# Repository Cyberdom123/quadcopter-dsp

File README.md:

# Quadcopter design made from scratch

The goal of the project is to create a working model of a quadcopter UAV, which can be
controlled with a Xbox controller. The project utilises the MPU6050 inertial measurement
unit, which combines MEMS accelerometer and gyroscope into a single IC. The combination of
sensor readings from the IMU combined with an adequate mathematical model and a regulating
system allows to make a quadcopter with a stable control system.

# Quadcopter project implementation

The MCU used in the project implementation is STM32F103C6T6, an ARM Cortex-M3 mi-
crocontroller, containing 32Kbytes of ROM. F1303 has built-in hardware support for I2C and
SPI busses used for data transmission between on-board peripherals.
The MPU6050 has been used as a sensor. It is an inertial measurement unit (IMU), a
MEMS integrated circuit combining in itself an accelerometer and a gyroscope. For easy and
intuitive reading of the sensor data at the code level, a library for initialising and handling the
MPU has been written. It uses the built-in I2C bus which is used to exchange data between the
IMU and MCU. The transmission is made in 400kHz mode. In order to save MCU execution
time, a DMA controller has been used, allowing for sending data from RAM to the peripheral.
Similarly, a library for nRF24L01 radio module has been written. nRF is being used for
digital radio transmission between the UAV and a PC. It is connected to the MCU by the
SPI bus and also uses the DMA mechanism. Another nRF connected to the PC is used to
communicate with the quadcopter. The transceivers are used in order to read telemetry data
and for piloting the UAV using an Xbox controller connected to the PC.

To keep the UAV stable it is essential to keep it at a set (stable) angle during movement.
For instance, when we want the drone to fly up vertically, the roll and pitch angle have to be
set to 0 degrees. The IMU supplies the data about displacement and angular velocity and a
suitable mathematical model processes the data in order to estimate the angles.
Finally the integration of data from both sensors with the help of filtration algorithms,
such as complementary filter or Kalman filter allows us to gain precise information about
the angles and for effective stabilisation of the quadcopter during flight. In our project we
used the Kalman filter. It is an aimed at estimating the actual state of the system based
on the observer measurements with Gaussian noise. The algorithm works in two main steps:
estimation of the state of the system based on previous state and correcting it during the next
measurement. Kalman filter uses the mathematical model and data about Gaussian noise in
order to minimalise the estimates and measurement unceirtanties.
The angle estimates and yaw angular velocity is fed into the regulation system consisitng
of three PID regulators for every quantity. The PID regulator works by minimising the difference
between the actual state of the system and a desirable reference state. It contains three
components: proportional (P), which reacts proportionally to current deviateion, integral (I),
which accumulates the deviation as time passes and differential (D), which takes into account
the rate of change of the difference. The output of the PIDs is a duty cycle fed into a signal
mixer, which sets the duty cycle for each of the motors.

More detailed documentation has been placed in the project repository.

## Part list

- Frame: https://www.thingiverse.com/thing:1604440
- 7mm Motor Holder: https://www.thingiverse.com/thing:1675767
- 7x20mm 3.7V DC 46500RPM Motors CCW
- 7x20mm 3.7V DC 46500RPM Motors CW
- Propellers: 55mm
- Transceiver: 2.4GHz NRF24L01
- LiPo Battery: 520mAh 25C 12g Dualsky
- Gyroscope/Accelerometer: MPU6050
- Pressure Sensor: BMP280
- STM32-FC Board (located in the hardware folder)

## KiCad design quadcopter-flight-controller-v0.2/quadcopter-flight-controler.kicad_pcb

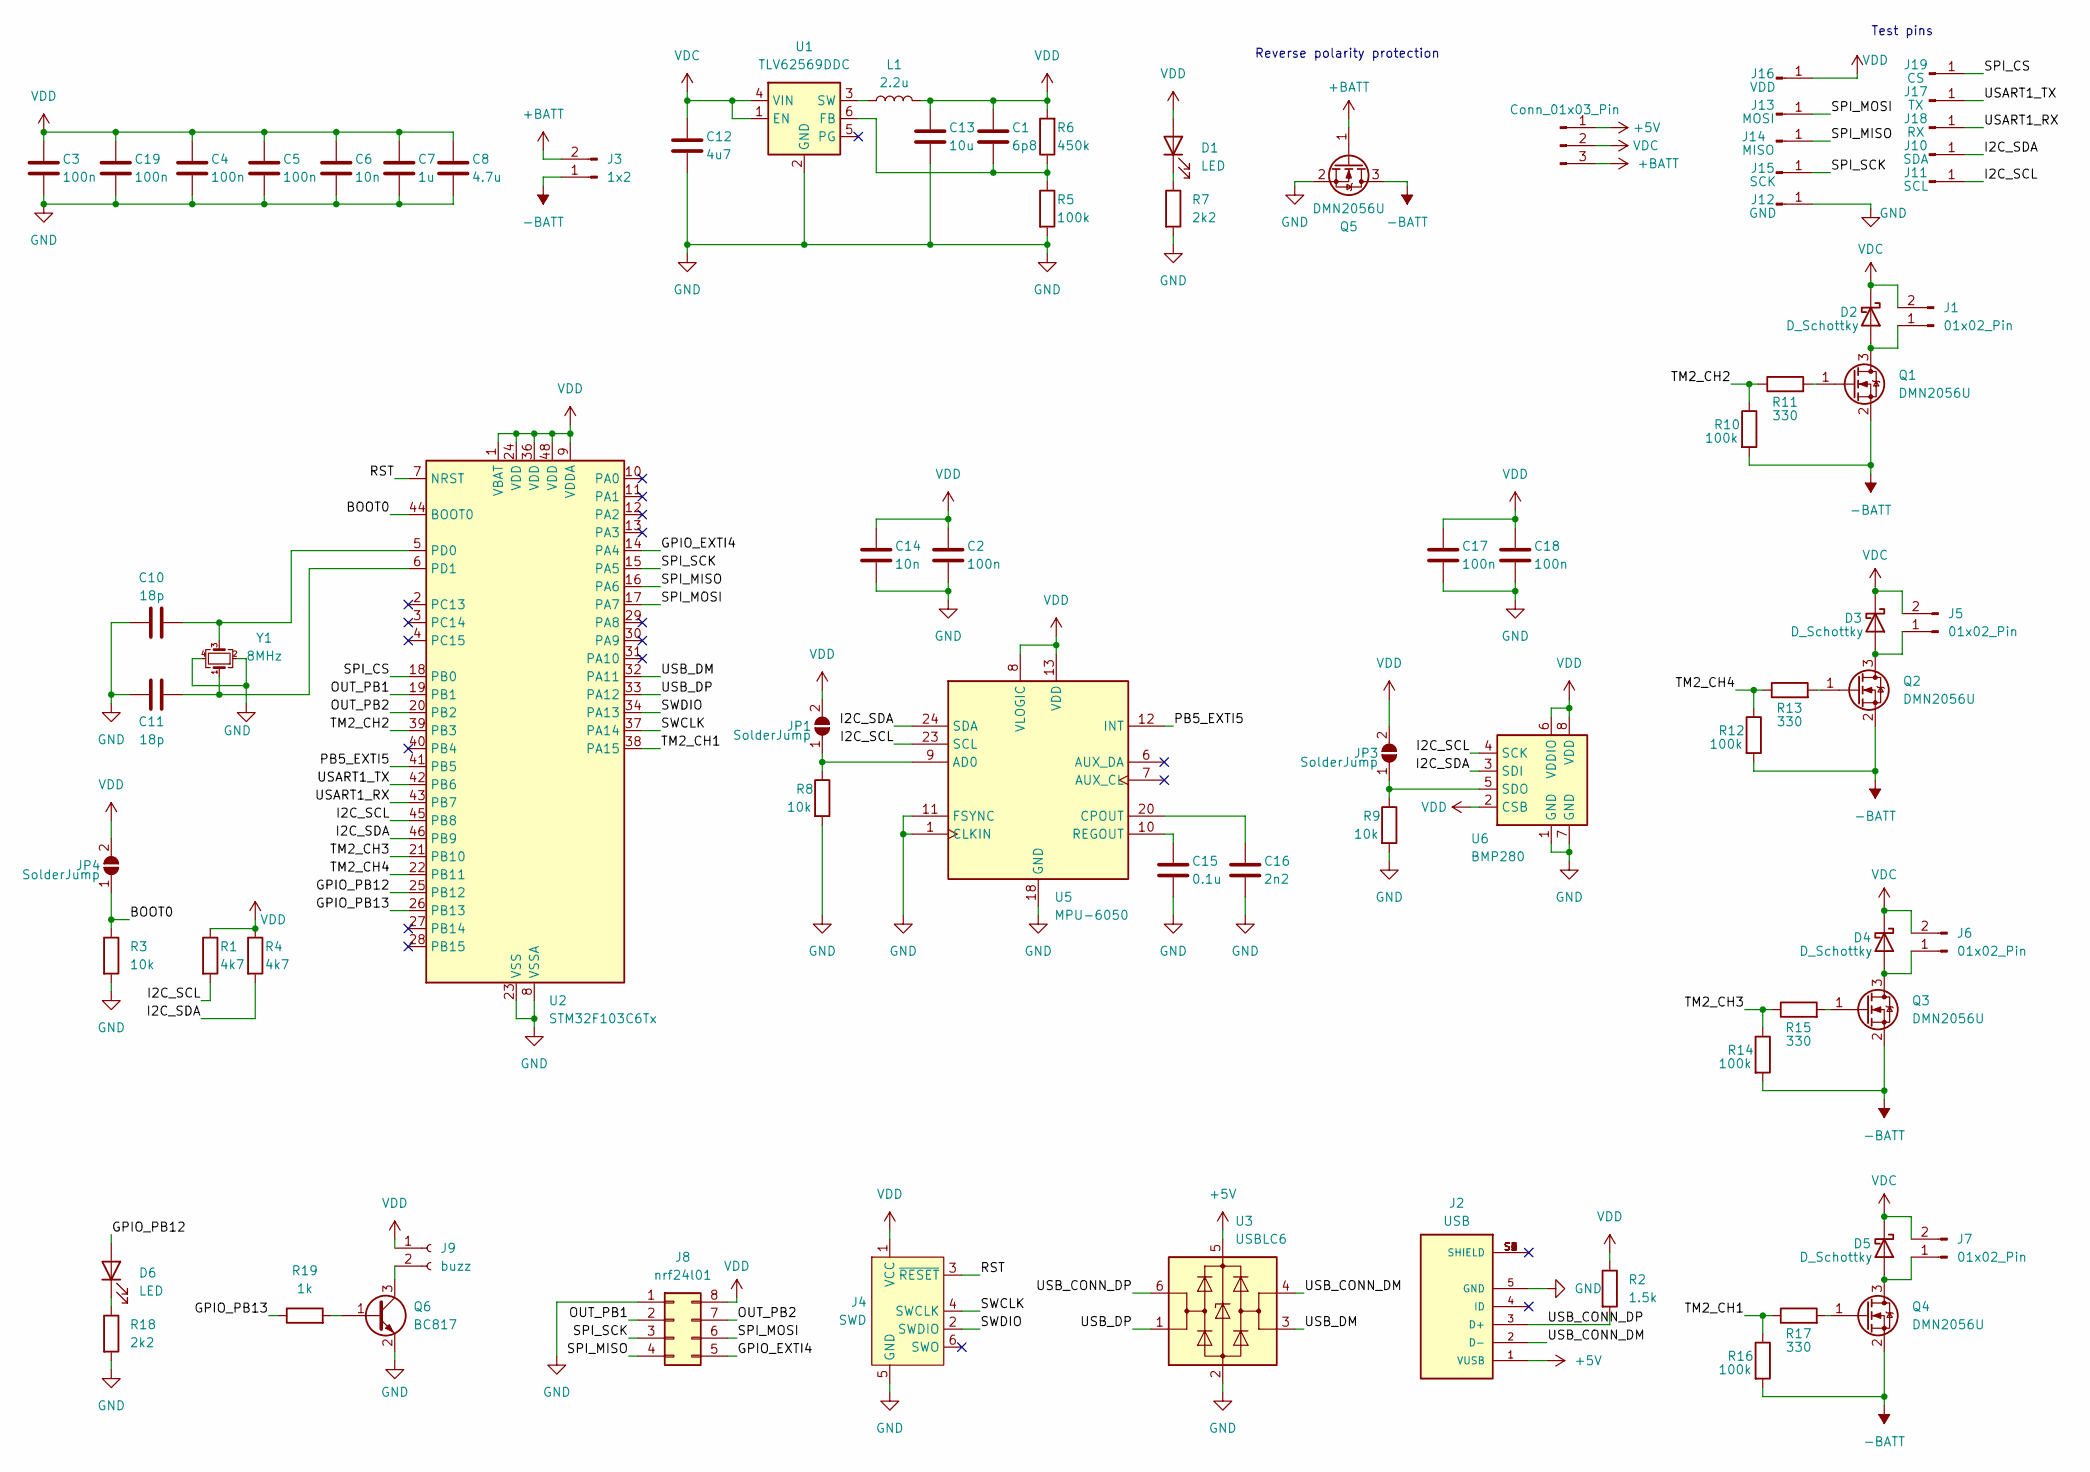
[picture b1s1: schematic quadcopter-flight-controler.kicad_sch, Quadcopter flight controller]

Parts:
C1: 6p8; C_0805_2012Metric
C2, C3, C4, C5, C17, C18, C19: 100n; C_0805_2012Metric
C6, C14: 10n; C_0805_2012Metric
C7: 1u; C_0805_2012Metric
C8: 4.7u; C_1206_3216Metric
C10, C11: 18p; C_0201_0603Metric
C12: 4u7; C_0805_2012Metric
C13: 10u; C_0805_2012Metric
C15: 0.1u; C_0805_2012Metric
C16: 2n2; C_0201_0603Metric
D1, D6: LED; LED_0805_2012Metric
D2, D3, D4, D5: D_Schottky; D_SOD-123F
J1, J5, J6, J7: 01x02_Pin; PinSocket_1x02_P1.27mm_Vertical
J2: USB; AMPHENOL_10118193-0001LF; PARTREV E
J3: 1x2; PinSocket_1x02_P2.54mm_Vertical
J4: SWD; Pin_2x03_P2.54mm
J8: nrf24l01; PinHeader_2x04_P2.54mm_Vertical
J9: buzz; PinSocket_1x02_P1.27mm_Vertical
J10: SDA; TestPoint_Pad_D1.0mm
J11: SCL; TestPoint_Pad_D1.0mm
J12: GND; TestPoint_Pad_D1.0mm
J13: MOSI; TestPoint_Pad_D1.0mm
J14: MISO; TestPoint_Pad_D1.0mm
J15: SCK; TestPoint_Pad_D1.0mm
J16: VDD; TestPoint_Pad_D1.0mm
J17: TX; TestPoint_Pad_D1.0mm
J18: RX; TestPoint_Pad_D1.0mm
J19: CS; TestPoint_Pad_D1.0mm
J20: Conn_01x03_Pin; PinSocket_1x03_P2.54mm_Vertical
JP1, JP3, JP4: SolderJump; SolderJumper-2_P1.3mm_Open_Pad1.0x1.5mm
L1: 2.2u; L_Coilcraft_XxL4040
Q1, Q2, Q3, Q4, Q5: DMN2056U; SOT-23
Q6: BC817; SOT-23
R1, R4: 4k7; R_0805_2012Metric
R2: 1.5k; R_0805_2012Metric
R3, R8, R9: 10k; R_0805_2012Metric
R5, R10, R12, R14, R16: 100k; R_0805_2012Metric
R6: 450k; R_0805_2012Metric
R7, R18: 2k2; R_0805_2012Metric
R11, R13, R15, R17: 330; R_0805_2012Metric
R19: 1k; R_0805_2012Metric
U1: TLV62569DDC; SOT-23-6
U2: STM32F103C6Tx; LQFP-48_7x7mm_P0.5mm
U3: USBLC6; SOT-23-6
U5: MPU-6050; InvenSense_QFN-24_4x4mm_P0.5mm
U6: BMP280; Bosch_LGA-8_2x2.5mm_P0.65mm_ClockwisePinNumbering
Y1: 8MHz; XTAL_QT532S-8.000MAAJ-T

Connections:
+5V: J2.1 (VUSB), J20.1, U3.5 (VBUS)
+BATT: J3.2, J20.3, Q5.1 (G)
-BATT: J3.1, Q1.2 (S), Q2.2 (S), Q3.2 (S), Q4.2 (S), Q5.3 (D), R10.2, R12.2, R14.2, R16.2
/BOOT0: JP4.1 (A), R3.1, U2.44 (BOOT0)
/GPIO_EXTI4: J8.5, U2.14 (PA4)
/GPIO_PB12: D6.2 (A), U2.25 (PB12)
/GPIO_PB13: R19.1, U2.26 (PB13)
/I2C_SCL: J11.1, R1.2, U2.45 (PB8), U5.23 (SCL), U6.4 (SCK)
/I2C_SDA: J10.1, R4.2, U2.46 (PB9), U5.24 (SDA), U6.3 (SDI)
/OUT_PB1: J8.2, U2.19 (PB1)
/OUT_PB2: J8.7, U2.20 (PB2)
/PB5_EXTI5: U2.41 (PB5), U5.12 (INT)
/RST: J4.3 (~RESET), U2.7 (NRST)
/SPI_CS: J19.1, U2.18 (PB0)
/SPI_MISO: J8.4, J14.1, U2.16 (PA6)
/SPI_MOSI: J8.6, J13.1, U2.17 (PA7)
/SPI_SCK: J8.3, J15.1, U2.15 (PA5)
/SWCLK: J4.4 (SWCLK), U2.37 (PA14)
/SWDIO: J4.2 (SWDIO), U2.34 (PA13)
/TM2_CH1: R16.1, R17.1, U2.38 (PA15)
/TM2_CH2: R10.1, R11.1, U2.39 (PB3)
/TM2_CH3: R14.1, R15.1, U2.21 (PB10)
/TM2_CH4: R12.1, R13.1, U2.22 (PB11)
/USART1_RX: J18.1, U2.43 (PB7)
/USART1_TX: J17.1, U2.42 (PB6)
/USB_CONN_DM: J2.2 (D-), U3.4 (I/O2)
/USB_CONN_DP: J2.3 (D+), R2.2, U3.6 (I/O1)
/USB_DM: U2.32 (PA11), U3.3 (I/O2)
/USB_DP: U2.33 (PA12), U3.1 (I/O1)
GND: C2.2, C3.2, C4.2, C5.2, C6.2, C7.2, C8.2, C10.1, C11.1, C12.2, C13.2, C14.2, C15.2, C16.2, C17.2, C18.2, C19.2, J2.5 (GND), J4.5 (GND), J8.1, J12.1, Q5.2 (S), Q6.2 (E), R3.2, R5.2, R7.2, R8.2, R9.2, R18.2, U1.2 (GND), U2.8 (VSSA), U2.23 (VSS), U2.35 (VSS), U2.47 (VSS), U3.2 (GND), U5.1 (CLKIN), U5.11 (FSYNC), U5.18 (GND), U6.1 (GND), U6.7 (GND), Y1.2, Y1.4
unnamed: D1.1 (K), R7.1
unnamed: D2.2 (A), J1.1, Q1.3 (D)
unnamed: D3.2 (A), J5.1, Q2.3 (D)
unnamed: D4.2 (A), J6.1, Q3.3 (D)
unnamed: D5.2 (A), J7.1, Q4.3 (D)
unnamed: D6.1 (K), R18.1
unnamed: J9.2, Q6.3 (C)
unnamed: JP1.1 (A), R8.1, U5.9 (AD0)
unnamed: JP3.1 (A), R9.1, U6.5 (SDO)
unnamed: Q1.1 (G), R11.2
unnamed: Q2.1 (G), R13.2
unnamed: Q3.1 (G), R15.2
unnamed: Q4.1 (G), R17.2
unnamed: Q6.1 (B), R19.2
unnamed: C1.2, R5.1, R6.1, U1.6 (FB)
unnamed: L1.1, U1.3 (SW)
unnamed: C10.2, U2.5 (PD0), Y1.3
unnamed: C11.2, U2.6 (PD1), Y1.1
unnamed: C16.1, U5.20 (CPOUT)
unnamed: C15.1, U5.10 (REGOUT)
VDC: C12.1, D2.1 (K), D3.1 (K), D4.1 (K), D5.1 (K), J1.2, J5.2, J6.2, J7.2, J20.2, U1.1 (EN), U1.4 (VIN)
VDD: C1.1, C2.1, C3.1, C4.1, C5.1, C6.1, C7.1, C8.1, C13.1, C14.1, C17.1, C18.1, C19.1, D1.2 (A), J4.1 (VCC), J8.8, J9.1, J16.1, JP1.2 (B), JP3.2 (B), JP4.2 (B), L1.2, R1.1, R2.1, R4.1, R6.2, U2.1 (VBAT), U2.9 (VDDA), U2.24 (VDD), U2.36 (VDD), U2.48 (VDD), U5.8 (VLOGIC), U5.13 (VDD), U6.2 (CSB), U6.6 (VDDIO), U6.8 (VDD)

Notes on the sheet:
Test pins
Reverse polarity protection

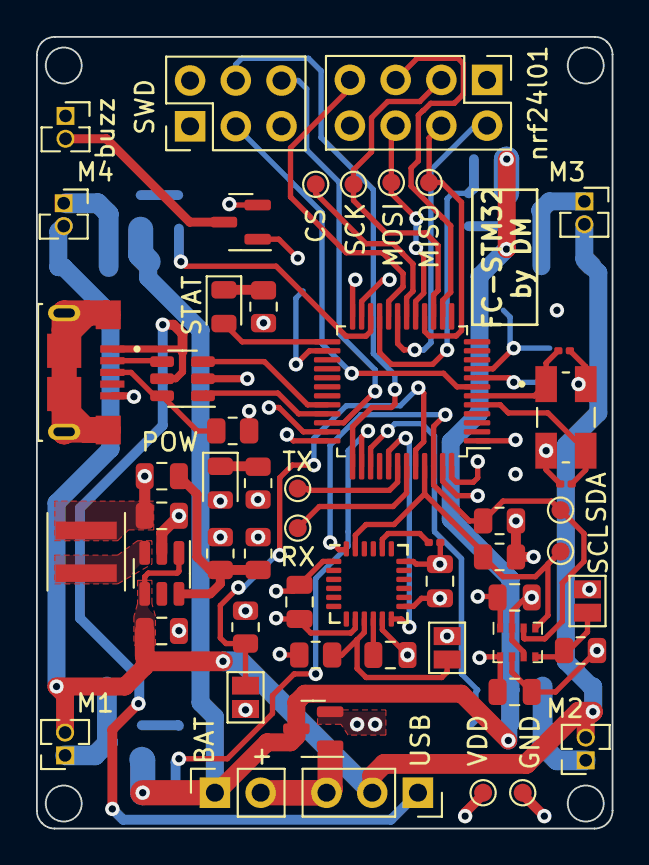
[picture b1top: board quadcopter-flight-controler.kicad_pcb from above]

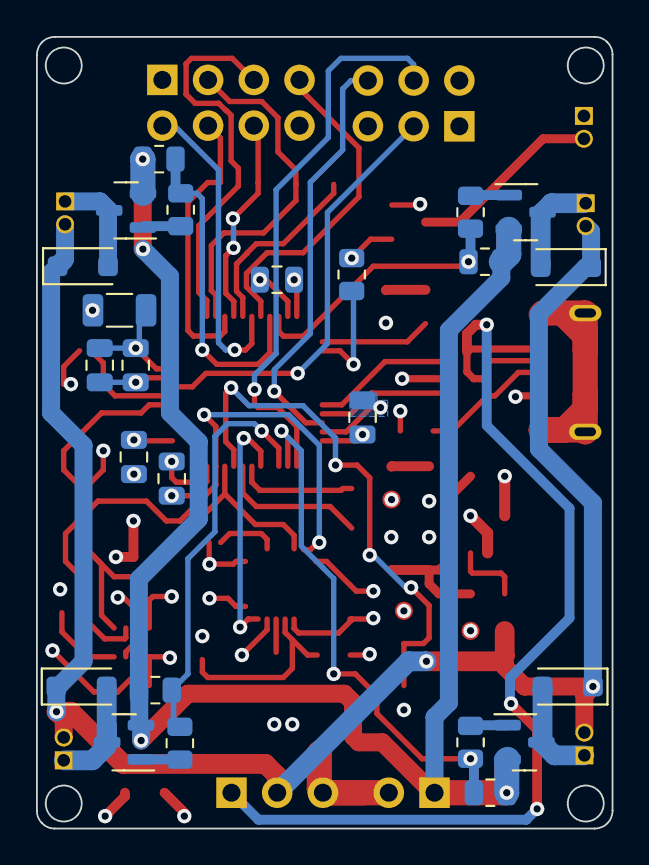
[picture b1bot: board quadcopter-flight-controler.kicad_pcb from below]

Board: 4 copper layers, 32.0 x 44.0 mm, 79 parts (24 on the bottom side), 52 nets.

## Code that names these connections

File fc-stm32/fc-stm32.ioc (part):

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Mcu.Name=STM32F103C(4-6)Tx
Mcu.Package=LQFP48
Mcu.UserName=STM32F103C6Tx
PA11.Mode=Device
PA11.Signal=USB_DM
PA12.Mode=Device
PA12.Signal=USB_DP
PA13.Mode=Serial_Wire
PA13.Signal=SYS_JTMS-SWDIO
PA14.Mode=Serial_Wire
PA14.Signal=SYS_JTCK-SWCLK
PA15.Signal=S_TIM2_CH1_ETR
PA4.Signal=GPXTI4
PA5.Mode=Full_Duplex_Master
PA5.Signal=SPI1_SCK
PA6.Mode=Full_Duplex_Master
PA6.Signal=SPI1_MISO
PA7.Mode=Full_Duplex_Master
PA7.Signal=SPI1_MOSI
PB1.GPIOParameters=GPIO_PuPd,GPIO_Label
PB1.GPIO_Label=CSN
PB1.GPIO_PuPd=GPIO_PULLUP
PB1.Signal=GPIO_Output
PB10.Signal=S_TIM2_CH3
PB11.Signal=S_TIM2_CH4
PB12.GPIOParameters=GPIO_Label
PB12.GPIO_Label=STATUS_LED
PB12.Signal=GPIO_Output
PB2.GPIOParameters=GPIO_PuPd,GPIO_Label
PB2.GPIO_Label=CE
PB2.GPIO_PuPd=GPIO_PULLUP
PB2.Signal=GPIO_Output
PB3.Signal=S_TIM2_CH2
PB8.Mode=I2C
PB8.Signal=I2C1_SCL
PB9.Mode=I2C
PB9.Signal=I2C1_SDA
PD0-OSC_IN.Mode=HSE-External-Oscillator
PD0-OSC_IN.Signal=RCC_OSC_IN
PD1-OSC_OUT.Mode=HSE-External-Oscillator
PD1-OSC_OUT.Signal=RCC_OSC_OUT
RCC.SYSCLKFreq_VALUE=72000000
RCC.SYSCLKSource=RCC_SYSCLKSOURCE_PLLCLK
board=custom

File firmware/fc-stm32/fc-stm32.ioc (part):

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Mcu.Name=STM32F103C(4-6)Tx
Mcu.Package=LQFP48
Mcu.UserName=STM32F103C6Tx
PA13.Mode=Serial_Wire
PA13.Signal=SYS_JTMS-SWDIO
PA14.Mode=Serial_Wire
PA14.Signal=SYS_JTCK-SWCLK
PA15.Signal=S_TIM2_CH1_ETR
PA4.GPIOParameters=GPIO_PuPd,GPIO_Label,GPIO_ModeDefaultEXTI
PA4.GPIO_Label=NRF_INT
PA4.GPIO_ModeDefaultEXTI=GPIO_MODE_IT_FALLING
PA4.GPIO_PuPd=GPIO_PULLUP
PA4.Signal=GPXTI4
PA5.Mode=Full_Duplex_Master
PA5.Signal=SPI1_SCK
PA6.Mode=Full_Duplex_Master
PA6.Signal=SPI1_MISO
PA7.Mode=Full_Duplex_Master
PA7.Signal=SPI1_MOSI
PB0.GPIOParameters=GPIO_Speed,GPIO_Label
PB0.GPIO_Label=SPI_CS
PB0.GPIO_Speed=GPIO_SPEED_FREQ_HIGH
PB0.Signal=GPIO_Output
PB1.GPIOParameters=GPIO_Speed,PinState,GPIO_PuPd,GPIO_Label
PB1.GPIO_Label=CSN
PB1.GPIO_PuPd=GPIO_PULLUP
PB1.GPIO_Speed=GPIO_SPEED_FREQ_HIGH
PB1.PinState=GPIO_PIN_SET
PB1.Signal=GPIO_Output
PB10.Signal=S_TIM2_CH3
PB11.Signal=S_TIM2_CH4
PB12.GPIOParameters=GPIO_Speed,GPIO_Label
PB12.GPIO_Label=STATUS_LED
PB12.GPIO_Speed=GPIO_SPEED_FREQ_HIGH
PB12.Signal=GPIO_Output
PB2.GPIOParameters=GPIO_Speed,GPIO_PuPd,GPIO_Label
PB2.GPIO_Label=CE
PB2.GPIO_PuPd=GPIO_PULLDOWN
PB2.GPIO_Speed=GPIO_SPEED_FREQ_HIGH
PB2.Signal=GPIO_Output
PB3.Signal=S_TIM2_CH2
PB5.GPIOParameters=GPIO_PuPd,GPIO_Label,GPIO_ModeDefaultEXTI
PB5.GPIO_Label=MPU_INT
PB5.GPIO_ModeDefaultEXTI=GPIO_MODE_IT_FALLING
PB5.GPIO_PuPd=GPIO_PULLUP
PB5.Signal=GPXTI5
PB8.Mode=I2C
PB8.Signal=I2C1_SCL
PB9.Mode=I2C
PB9.Signal=I2C1_SDA
PD0-OSC_IN.Mode=HSE-External-Oscillator
PD0-OSC_IN.Signal=RCC_OSC_IN
PD1-OSC_OUT.Mode=HSE-External-Oscillator
PD1-OSC_OUT.Signal=RCC_OSC_OUT
RCC.SYSCLKFreq_VALUE=72000000
RCC.SYSCLKSource=RCC_SYSCLKSOURCE_PLLCLK
board=custom

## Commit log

2023-08-12 new pcb
2023-09-14 nrf24-lib, stm32-fc-tests
2023-09-14 kicad-files
2023-09-19 some tests
2023-09-19 moved tests to `firmware/tests`; moved main firmware to `firmware`; added `software` folder
2023-09-19 added basic MPU functions and definitions for MPU registers, it compiles, not tested yet
2023-09-21 added simple test for mpu
2023-09-21 added todo tree config to settings.json
2023-09-21 controller_script_improvements
2023-09-22 fixed address issues
2023-09-22 merged settings json i guess
2023-09-22 commited .vscode
2023-09-22 fixed settings.json
2023-09-22 asdasdsa
2023-09-22 added common settings.json settings for todotree
2023-09-22 added gitignore
2023-09-22 interrupt fix
2023-09-22 device power down
2023-09-22 ignore this commit
2023-09-23 prettier comments
2023-09-23 Spi transmit-recieve implementation
2023-09-24 SPI DMA
2023-09-24 removing .vscode
2023-09-24 fixing .vscode
2023-09-25 Radio control improvement
    * rc
    * controller_script_improvements
    * interrupt fix
    * device power down
    * prettier comments
    * Spi transmit-recieve implementation
2023-09-28 added the register map, corrected some register names
2023-09-28 added all registers to register map, got rid of some magic numbers
2023-09-29 motors-algorithm
2023-09-29 added fullscale range enums
2023-10-01 expanded mpu config struct with additional settings
2023-10-02 mpu tested, acc pass
2023-10-02 expanded config struct; changed mpu output to float
2023-10-03 nrf_cfg struct, motors.h
2023-10-04 changed implementation od MPU_init to use resolution setters; fixed a bug, where acc and gyro reads returned wrong values
2023-10-04 added enum for int logic level in config
2023-10-04 fixed typo in enum
2023-10-04 tested all changes
2023-10-05 custom sprintf implementation
2023-10-07 USB-VPC
2023-10-07 optimized implementation of sprintf is now working
2023-10-07 removed .vscode, usb disabled
2023-10-07 reorganized source tree, changed compiler optimization to -Os, added new source dirs
2023-10-09 pid implementation
2023-10-09 descryption
2023-10-12 successfully enabled ack payload
2023-10-15 fixed bugs
2023-10-15 removed .vscode
2023-10-16 Ack npayload (#8)
    * successfully enabled ack payload
    * fixed bugs
    * removed .vscode
2023-10-18 python filters simulations
2023-10-20 ACK payloads
2023-10-20 added rudimentary EMA filter, not tested yet
2023-10-23 added alpha calculations
2023-10-23 Added support for DMA in MPU6050 driver, yet to be tested
2023-10-31 added interrupts tests
2023-11-14 mpu int working
2023-11-15 fixed readings
2023-11-15 added trasmitter firmware
2023-11-16 improved logging routine
2023-11-22 accelerometer pitch, roll estimation
2023-11-22 removed .pio
2023-11-22 filter tests, logged sample data from accelerometer
2023-11-26 hardware low-pass filter enabled
2023-11-26 Added gyro offset compensation, moved mpu interrupt clear from init to main
2023-12-05 control loop tests
2023-12-06 additional filtering added
2023-12-07 added function for updating euler angles base on gyro readings
2023-12-07 added a comment
2023-12-08 added axes remapping that hopefully fixes the estimation problems
2023-12-08 complementary
2023-12-08 fixed rotation matrix
2023-12-08 fixed bugs in complementary filter
2023-12-08 complementary filter now working fine
2023-12-09 Control loop test with complementary filter
2023-12-11 first flight test
2023-12-14 IIR filters calculations
2023-12-19 filter design
2023-12-21 band pass filter calculations
2023-12-21 added some filter prototypes
2023-12-21 low pass testing
2023-12-22 taylor stuff
2023-12-26 spi flash logger
2023-12-26 logger interface
2023-12-26 Logger (#13)
    * spi flash logger
    * logger interface
2023-12-26 first working prototype
2024-01-01 added low pass filter
2024-01-02 one dimensional kalman filter
2024-01-03 radio control upgrade
2024-01-03 added a better way to send data in gamepad script
2024-01-04 the stabilization algorithm now uses a kalman filter
2024-01-22 added photos
2024-01-23 updated docs
2024-01-25 fixed bugs, added flash_memory lib, imporved controller script
2024-01-25 added missing files (rc-timeout, linker)
2024-01-26 added missing files descriptions
2024-02-05 updated radio code
2024-02-10 added CmakeLists.txt
2024-02-24 ld issue
2024-02-25 replaced build system with cmake
2024-02-26 added makeflie
2024-02-27 vscode cfg
2024-02-27 eanbled debugging with openOCD and gdb
2024-02-27 Cmake build sys (#16)
    * added CmakeLists.txt
    * ld issue
    * replaced build system with cmake
    * added makeflie
    * vscode cfg
    * eanbled debugging with openOCD and gdb
2024-02-28 removed .vscode, changed files location
2024-04-05 bmp280 lib
2024-07-16 removed unused lib
2024-07-16 ibus driver
2024-07-16 project cleanup
2024-07-16 further cleanup
2024-08-04 FIX: MPU wrong address
2024-08-15 work in progress
2024-08-15 WIP: high level api
2024-09-05 WIP: rework
2024-09-13 WIP: improved build system
2024-09-17 extended stm32 hal library
2024-09-19 working version
2024-09-20 fixes
2024-09-22 add 0s flag to debug build, moved interrupts handlers to main
2024-09-22 further wrok
2024-09-29 Fix .gitignore formatting issue
2024-11-09 refine PID parameters
